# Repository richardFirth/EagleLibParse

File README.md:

# EagleLibParse

*WORK IN PROGRESS*

VBA to parse eagle library files

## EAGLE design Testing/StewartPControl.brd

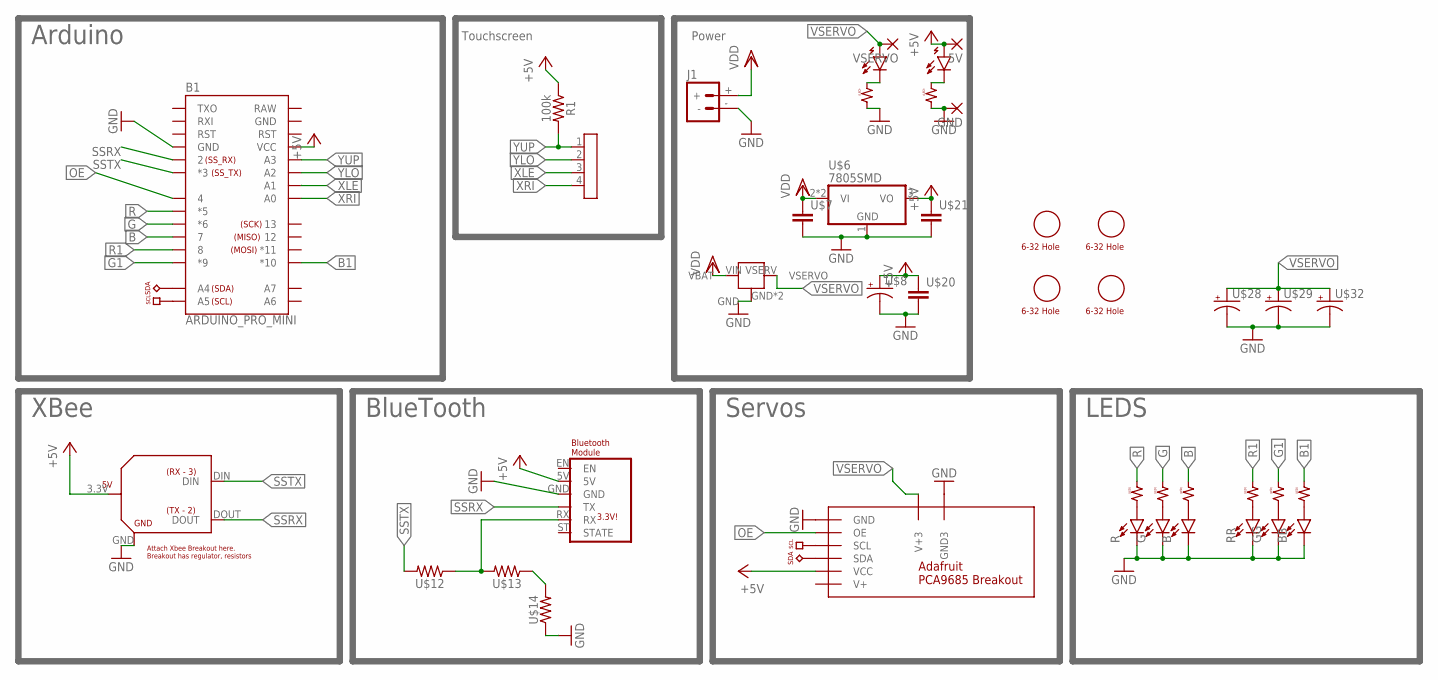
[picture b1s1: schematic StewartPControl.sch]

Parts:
5V: PADNRML; PAD_NRML
B: LEDSMD; LED_SMD
B1: ARDUINO_PRO_MINI
BB: LEDSMD; LED_SMD
G: LEDSMD; LED_SMD
GG: LEDSMD; LED_SMD
GND: PADNRML; PAD_NRML
J1: BATTERY_CONNMALE; DEANS_MALE
R: LEDSMD; LED_SMD
R1: 100k; RESISTOR
RR: LEDSMD; LED_SMD
U$1: ADA_PCA9685
U$2: XBEE_BOUT_5; XBEE_BOUT
U$5: 4XHEADER
U$6: 7805SMD; SOT223
U$7, U$21: CAP_SMCAP; C1206
U$8, U$28, U$29, U$32: CAP_EMED; CAP_E
U$9, U$23: POW_LED; POW_LED_SMD
U$10, U$22, U$27: LED_RESISTORSMD; LED_R1206
U$11: BT_HC05
U$12, U$13, U$14: RESISTORSMD; R1206
U$15: CASTLE_BEC
U$16, U$17, U$18, U$19: 632
U$20: CAP_SMNORM; CAP_SM
U$24, U$25, U$26, U$30, U$31: LED_RESISTORNORMAL; LED_RESISTOR
VSERVO: PADNRML; PAD_NRML

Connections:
+5V: 5V.P$2, B1.21 (VCC), R1.P$1 (1), U$1.VCC, U$1.VCC2 (VCC), U$2.3.3V, U$6.3 (VO), U$8.+, U$9.A, U$11.5V, U$20.1, U$21.1
B: B1.10 (7), U$30.P$2 (2)
B1: B1.13 (*10), U$27.2
G: B1.9 (*6), U$24.P$2 (2)
G1: B1.12 (*9), U$26.P$2 (2)
GND: B.C, B1.4 (GND), B1.23 (GND), BB.C, G.C, GG.C, GND.P$2, J1.-, R.C, RR.C, U$1.GND, U$1.GND2 (GND), U$1.GND3, U$2.GND, U$6.1 (GND), U$7.2, U$8.-, U$10.1, U$11.GND, U$14.1, U$15.GND, U$15.GND2 (GND), U$20.2, U$21.2, U$22.1, U$28.-, U$29.-, U$32.-
unnamed: U$13.1, U$14.2
unnamed: U$9.C, U$10.2
unnamed: U$11.RX, U$12.1, U$13.2
unnamed: U$22.2, U$23.C
unnamed: G.A, U$24.P$1 (1)
unnamed: B.A, U$30.P$1 (1)
unnamed: R.A, U$31.P$1 (1)
unnamed: RR.A, U$25.P$1 (1)
unnamed: GG.A, U$26.P$1 (1)
unnamed: BB.A, U$27.1
OE: B1.7 (4), U$1.OE, U$1.OE2 (OE)
R: B1.8 (*5), U$31.P$2 (2)
R1: B1.11 (8), U$25.P$2 (2)
RAW: B1.24 (RAW)
SCL: B1.A5, U$1.SCL, U$1.SCL2 (SCL)
SDA: B1.A4, U$1.SDA, U$1.SDA2 (SDA)
SSRX: B1.5 (2), U$2.DOUT, U$11.TX
SSTX: B1.6 (*3), U$2.DIN, U$12.2
VDD: J1.+, U$6.2 (VI), U$6.4 (VI), U$7.1, U$15.VIN (VBAT)
VSERVO: U$1.V+3, U$15.VSERV (VSERVO), U$23.A, U$28.+, U$29.+, U$32.+, VSERVO.P$2
XLE: B1.18 (A1), U$5.3
XRI: B1.17 (A0), U$5.4
YLO: B1.19 (A2), U$5.2
YUP: B1.20 (A3), R1.P$2 (2), U$5.1

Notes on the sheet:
Arduino
Touchscreen
Power
XBee
BlueTooth
Servos
LEDS

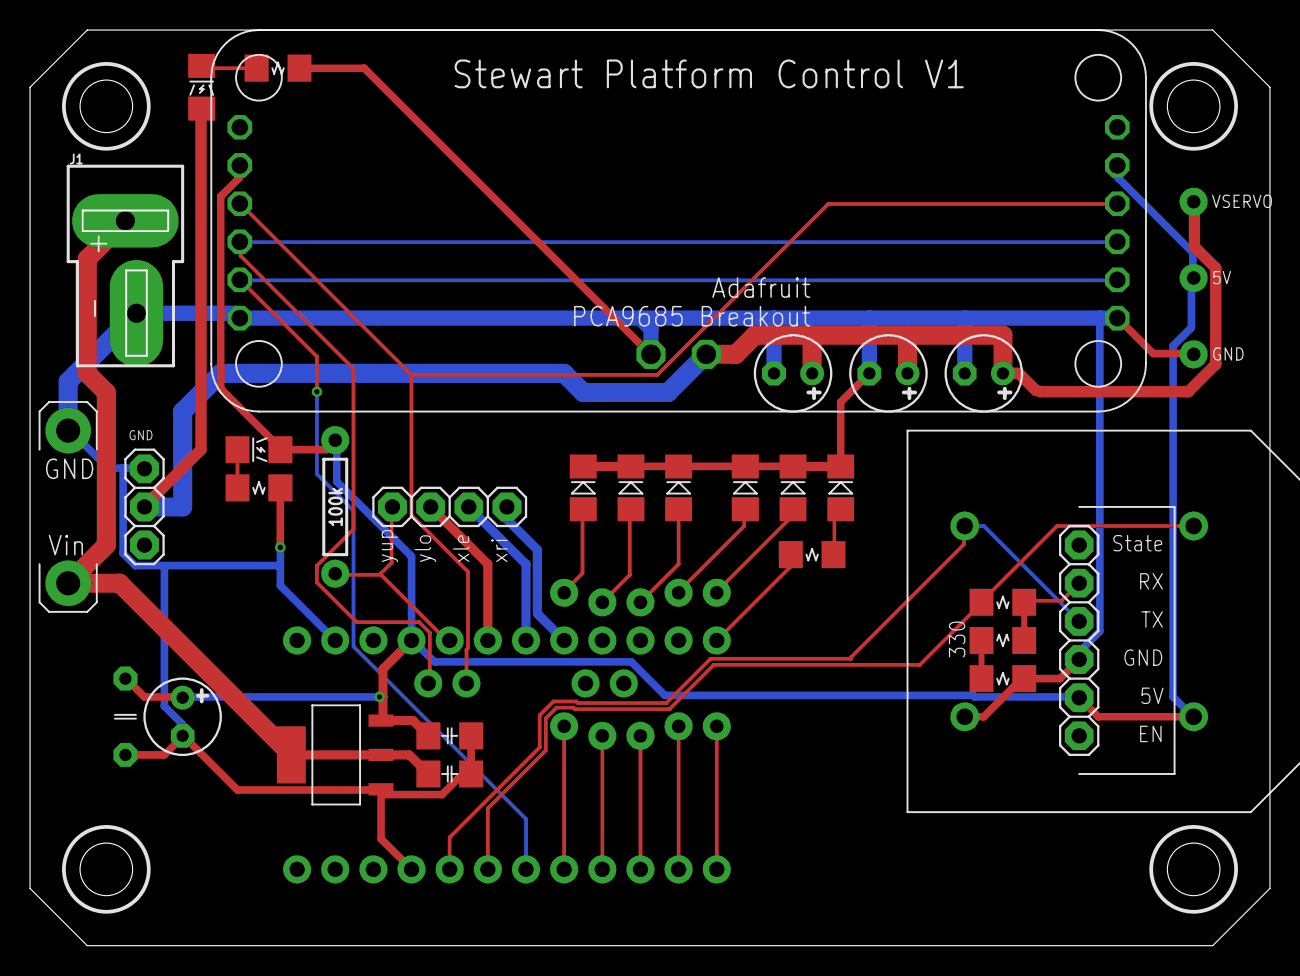
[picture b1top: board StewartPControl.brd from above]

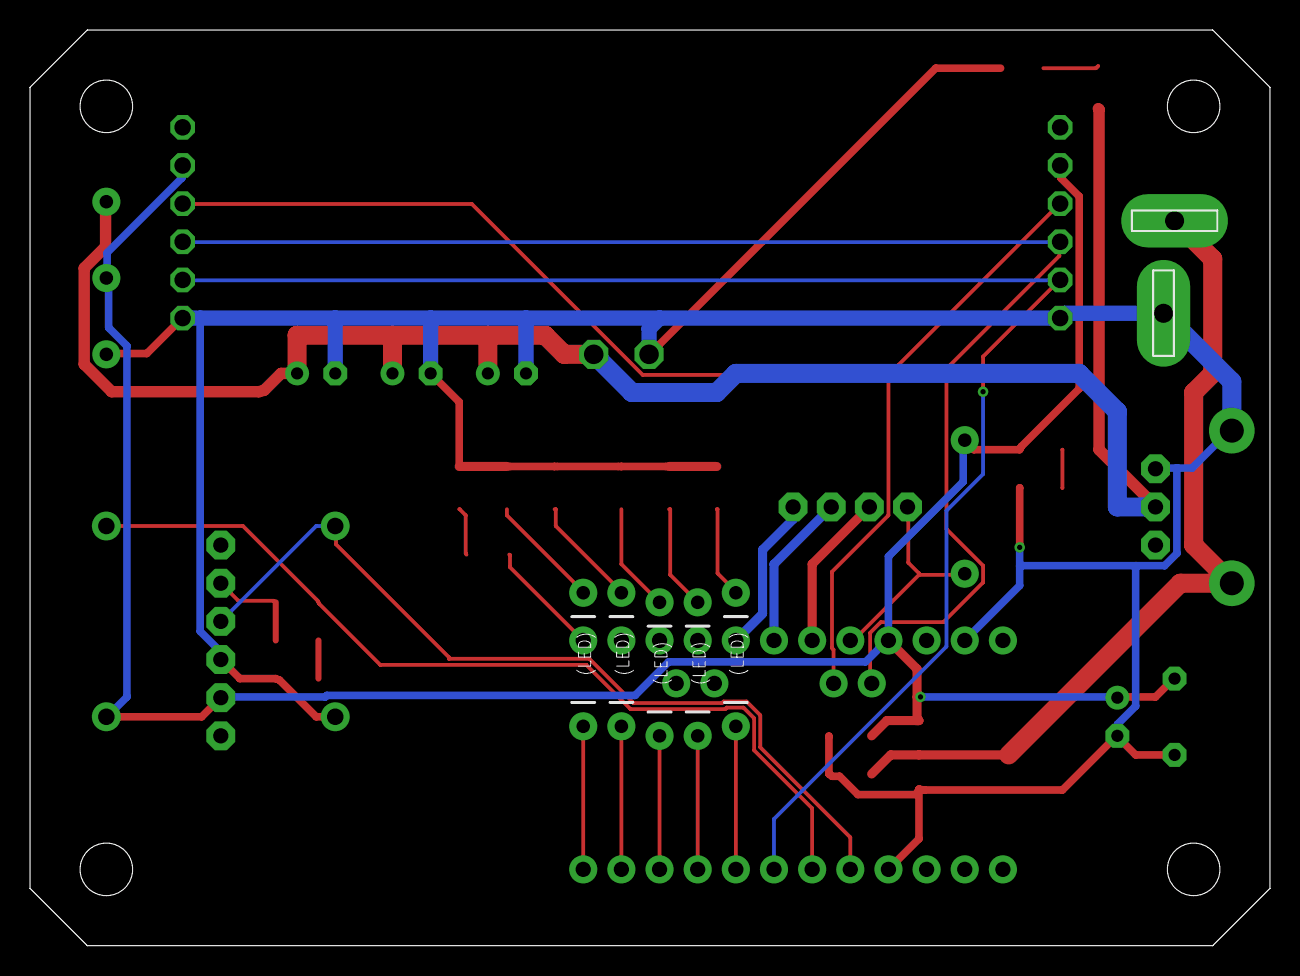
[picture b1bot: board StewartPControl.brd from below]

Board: 2 copper layers, 82.4 x 60.8 mm, 42 parts (5 on the bottom side), 29 nets.

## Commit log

2018-02-19 cleanup exta stuff, resync
2018-02-25 sync mods, add template
2018-03-10 update libs, refresh macro
2018-04-02 update it
2018-04-03 add extra
2018-04-03 rename
2018-04-08 add chip create
2018-04-08 update IC lib
2018-04-10 mod empty lib
2018-04-10 update UI, add chipcreator
2018-04-11 modify
2018-04-12 add the MCP9808
2018-04-12 add export, templates, and update EagLIB
2018-04-12 fix tables
2018-04-14 modify macro
2018-04-19 latest
2018-04-19 update templates
